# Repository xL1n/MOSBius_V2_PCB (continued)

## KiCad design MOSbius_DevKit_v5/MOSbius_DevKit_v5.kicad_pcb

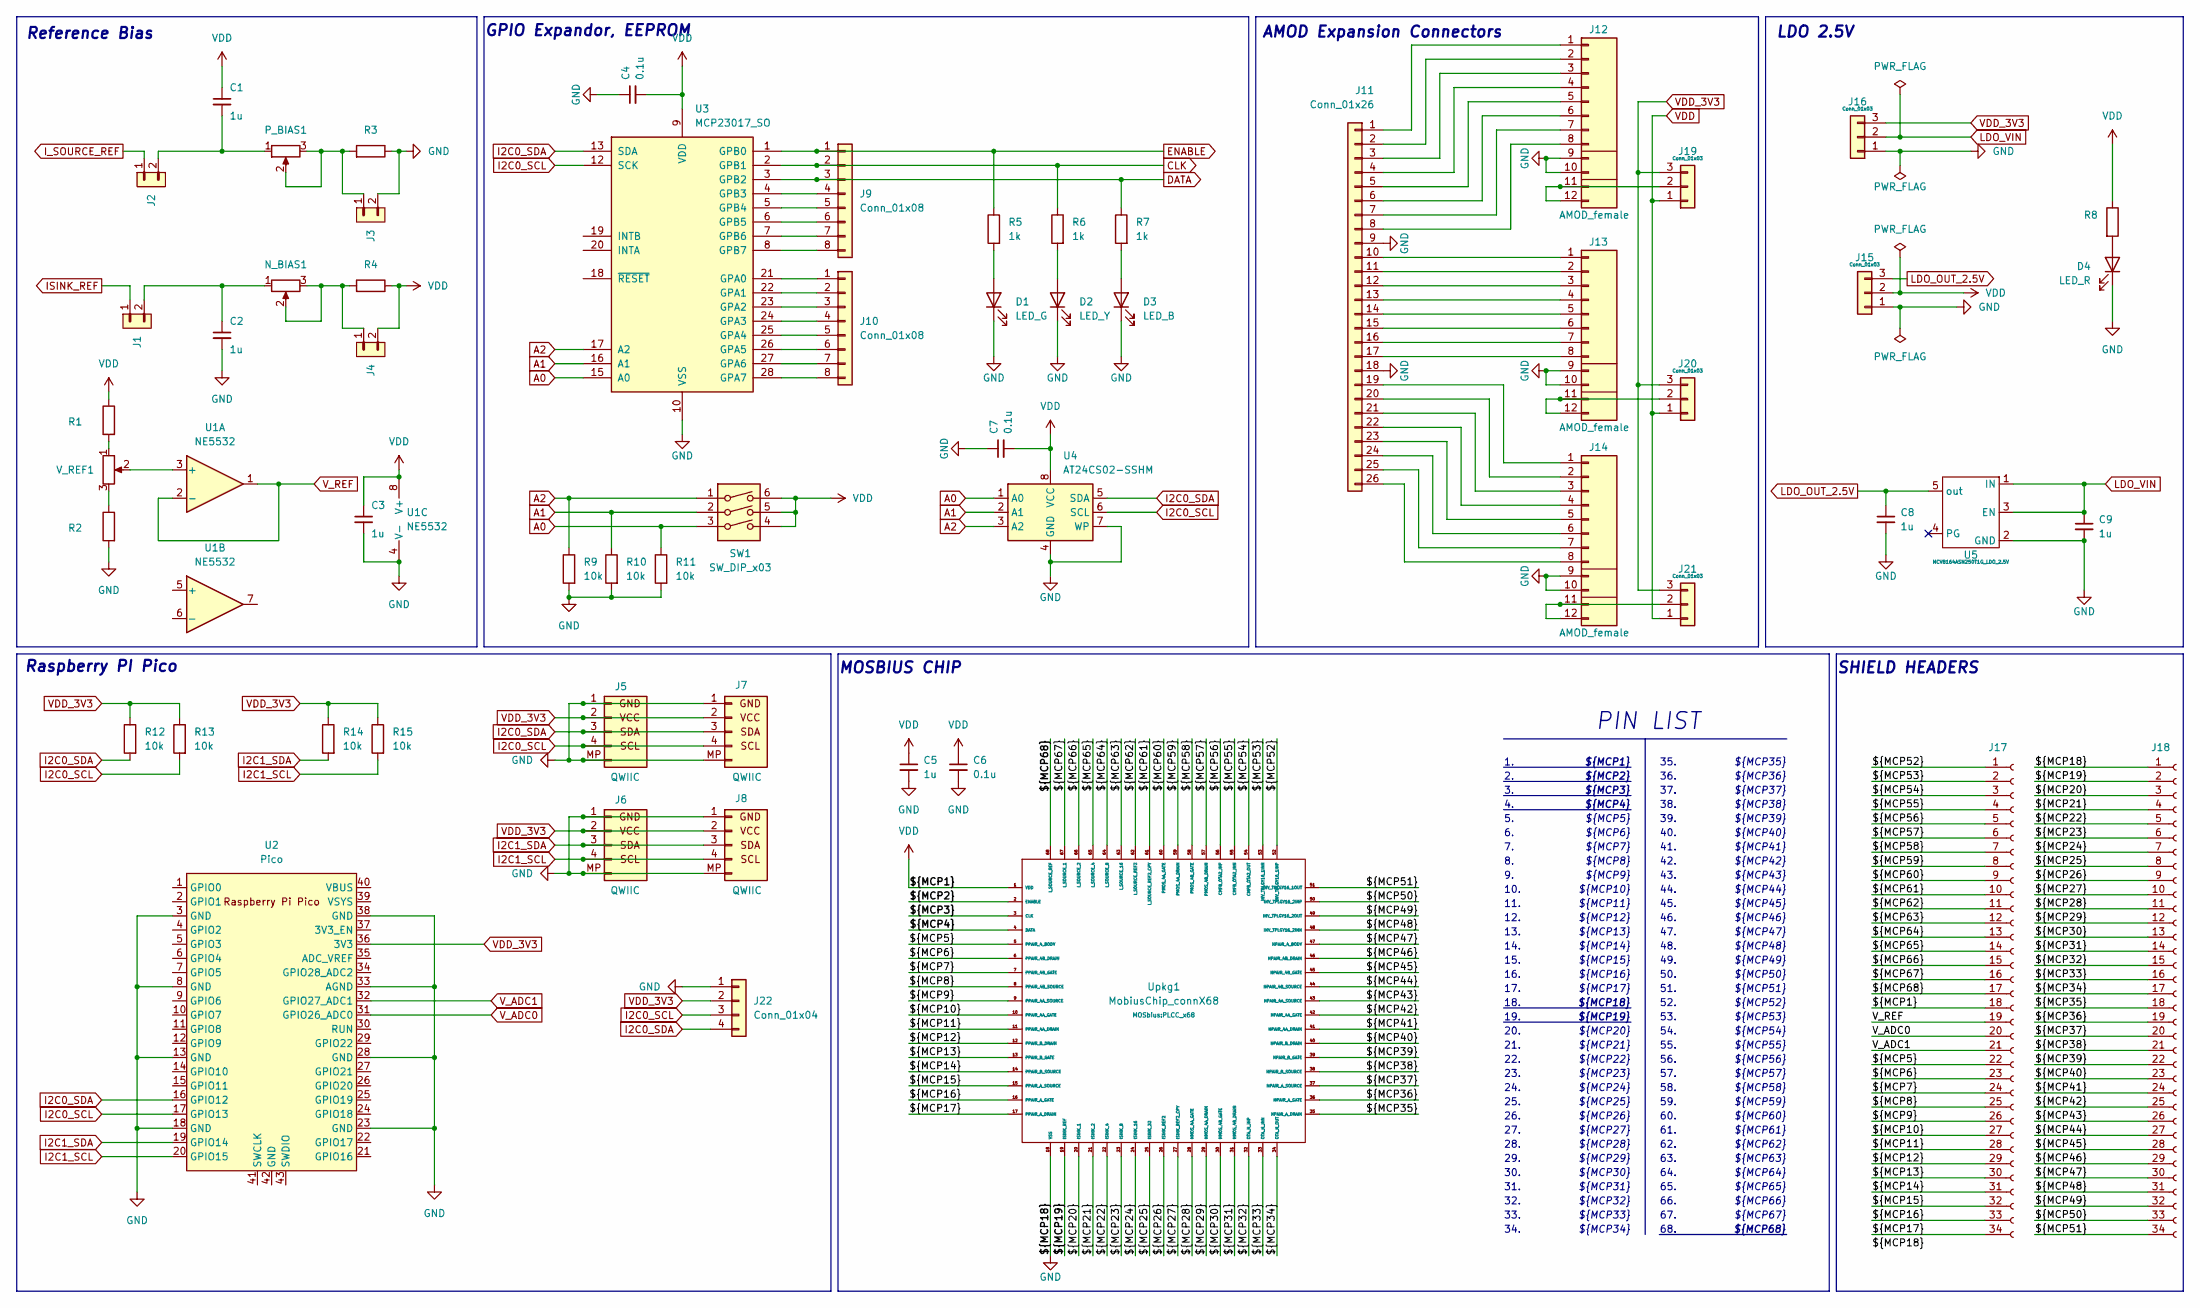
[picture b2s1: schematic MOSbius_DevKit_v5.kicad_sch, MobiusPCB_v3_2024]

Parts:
C1, C2, C3, C5, C8, C9: 1u; C_0603_1608Metric
C4, C6, C7: 0.1u; C_0603_1608Metric
D1: LED_G; LED_0805_2012Metric
D2: LED_Y; LED_0805_2012Metric
D3: LED_B; LED_0805_2012Metric
D4: LED_R; LED_0805_2012Metric
J1, J2, J3, J4: PINHD_1x2_Male; PinHeader_1x02_P2.54mm_Vertical
J5, J6, J7, J8: QWIIC; JST_SH_SM04B-SRSS-TB_1x04-1MP_P1.00mm_Horizontal
J9, J10: Conn_01x08; PinHeader_1x08_P2.54mm_Vertical
J11: Conn_01x26; PinHeader_1x26_P2.54mm_Vertical
J12, J13, J14: AMOD_female
J15, J16, J19, J20, J21: Conn_01x03; PinHeader_1x03_P2.54mm_Vertical
J17, J18: Conn_01x34_Socket; PinHeader_1x34_P2.54mm_Vertical
J22: Conn_01x04; PinHeader_1x04_P2.54mm_Vertical
N_BIAS1: R_Potentiometer; Potentiometer_Bourns_3296W_Vertical
P_BIAS1: R_Potentiometer; Potentiometer_Bourns_3296W_Vertical
R1, R2, R3, R4: 1.3K; R_0603_1608Metric
R5, R6, R7, R8: 1k; R_0603_1608Metric
R9, R10, R11, R12, R13, R14, R15: 10k; R_0603_1608Metric
SW1: SW_DIP_x03; SW_DIP_SPSTx03_Slide_Omron_A6S-310x_W8.9mm_P2.54mm
U1: NE5532
U2: Pico; RPi_Pico_SMD_TH
U3: MCP23017_SO; SOIC-28W_7.5x17.9mm_P1.27mm
U4: AT24CS02-SSHM; SOIC-8_3.9x4.9mm_P1.27mm
U5: NCV8164ASN250T1G_LDO_2.5V; SOT-23-5
Upkg1: MobiusChip_connX68; PLCC_x68
V_REF1: R_Potentiometer; Potentiometer_Bourns_3296W_Vertical

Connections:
/CMFB_OTA2_INN: J17.4, Upkg1.55 (CMFB_OTA2_INN)
/CMFB_OTA2_INP: J17.5, Upkg1.56 (CMFB_OTA2_INP)
/CMFB_OTA2_OUT: J17.3, Upkg1.54 (CMFB_OTA2_OUT)
/INV_TPLGY16_1INN: J17.2, Upkg1.53 (INV_TPLGY16_1INN)
/INV_TPLGY16_1INP: J17.1, Upkg1.52 (INV_TPLGY16_1INP)
/INV_TPLGY16_1OUT: J18.34, Upkg1.51 (INV_TPLGY16_1OUT)
/INV_TPLGY16_2INN: J18.31, Upkg1.48 (INV_TPLGY16_2INN)
/INV_TPLGY16_2INP: J18.33, Upkg1.50 (INV_TPLGY16_2INP)
/INV_TPLGY16_2OUT: J18.32, Upkg1.49 (INV_TPLGY16_2OUT)
/ISINK_1: J18.3, Upkg1.20 (ISINK_1)
/ISINK_2: J18.4, Upkg1.21 (ISINK_2)
/ISINK_4: J18.5, Upkg1.22 (ISINK_4)
/ISINK_8: J18.6, Upkg1.23 (ISINK_8)
/ISINK_16: J18.7, Upkg1.24 (ISINK_16)
/ISINK_32: J18.8, Upkg1.25 (ISINK_32)
/ISINK_REF2: J18.9, Upkg1.26 (ISINK_REF2)
/ISINK_REF2_CPY: J18.10, Upkg1.27 (ISINK_REF2_CPY)
/I_SOURCE_1: J17.16, Upkg1.67 (I_SOURCE_1)
/I_SOURCE_2: J17.15, Upkg1.66 (I_SOURCE_2)
/I_SOURCE_4: J17.14, Upkg1.65 (I_SOURCE_4)
/I_SOURCE_8: J17.13, Upkg1.64 (I_SOURCE_8)
/I_SOURCE_16: J17.12, Upkg1.63 (I_SOURCE_16)
/I_SOURCE_REF2: J17.11, Upkg1.62 (I_SOURCE_REF2)
/I_SOURCE_REF2_CPY: J17.10, Upkg1.61 (I_SOURCE_REF2_CPY)
/NMOS_4A_DRAIN: J18.12, Upkg1.29 (NMOS_4A_DRAIN)
/NMOS_4A_GATE: J18.11, Upkg1.28 (NMOS_4A_GATE)
/NMOS_4B_DRAIN: J18.14, Upkg1.31 (NMOS_4B_DRAIN)
/NMOS_4B_GATE: J18.13, Upkg1.30 (NMOS_4B_GATE)
/NPAIR_4A_DRAIN: J18.24, Upkg1.41 (NPAIR_4A_DRAIN)
/NPAIR_4A_GATE: J18.25, Upkg1.42 (NPAIR_4A_GATE)
/NPAIR_4A_SOURCE: J18.26, Upkg1.43 (NPAIR_4A_SOURCE)
/NPAIR_4B_DRAIN: J18.29, Upkg1.46 (NPAIR_4B_DRAIN)
/NPAIR_4B_GATE: J18.28, Upkg1.45 (NPAIR_4B_GATE)
/NPAIR_4B_SOURCE: J18.27, Upkg1.44 (NPAIR_4B_SOURCE)
/NPAIR_4_BODY: J18.30, Upkg1.47 (NPAIR_4_BODY)
/NPAIR_A_DRAIN: J18.18, Upkg1.35 (NPAIR_A_DRAIN)
/NPAIR_A_GATE: J18.19, Upkg1.36 (NPAIR_A_GATE)
/NPAIR_A_SOURCE: J18.20, Upkg1.37 (NPAIR_A_SOURCE)
/NPAIR_B_DRAIN: J18.23, Upkg1.40 (NPAIR_B_DRAIN)
/NPAIR_B_GATE: J18.22, Upkg1.39 (NPAIR_B_GATE)
/NPAIR_B_SOURCE: J18.21, Upkg1.38 (NPAIR_B_SOURCE)
/OTA_N_INN: J18.16, Upkg1.33 (OTA_N_INN)
/OTA_N_INP: J18.15, Upkg1.32 (OTA_N_INP)
/OTA_N_OUT: J18.17, Upkg1.34 (OTA_N_OUT)
/PMOS_4A_DRAIN: J17.8, Upkg1.59 (PMOS_4A_DRAIN)
/PMOS_4A_GATE: J17.9, Upkg1.60 (PMOS_4A_GATE)
/PMOS_4B_DRAIN: J17.6, Upkg1.57 (PMOS_4B_DRAIN)
/PMOS_4B_GATE: J17.7, Upkg1.58 (PMOS_4B_GATE)
/PPAIR_4A_DRAIN: J17.28, Upkg1.11 (PPAIR_4A_DRAIN)
/PPAIR_4A_GATE: J17.27, Upkg1.10 (PPAIR_4A_GATE)
/PPAIR_4A_SOURCE: J17.26, Upkg1.9 (PPAIR_4A_SOURCE)
/PPAIR_4B_DRAIN: J17.23, Upkg1.6 (PPAIR_4B_DRAIN)
/PPAIR_4B_GATE: J17.24, Upkg1.7 (PPAIR_4B_GATE)
/PPAIR_4B_SOURCE: J17.25, Upkg1.8 (PPAIR_4B_SOURCE)
/PPAIR_4_BODY: J17.22, Upkg1.5 (PPAIR_4_BODY)
/PPAIR_A_DRAIN: J17.34, Upkg1.17 (PPAIR_A_DRAIN)
/PPAIR_A_GATE: J17.33, Upkg1.16 (PPAIR_A_GATE)
/PPAIR_A_SOURCE: J17.32, Upkg1.15 (PPAIR_A_SOURCE)
/PPAIR_B_DRAIN: J17.29, Upkg1.12 (PPAIR_B_DRAIN)
/PPAIR_B_GATE: J17.30, Upkg1.13 (PPAIR_B_GATE)
/PPAIR_B_SOURCE: J17.31, Upkg1.14 (PPAIR_B_SOURCE)
A0: R11.1, SW1.3, U3.15 (A0), U4.1 (A0)
A1: R10.1, SW1.2, U3.16 (A1), U4.2 (A1)
A2: R9.1, SW1.1, U3.17 (A2), U4.3 (A2)
GND: C2.2, C3.2, C4.1, C5.2, C6.2, C7.1, C8.2, C9.2, D1.1 (K), D2.1 (K), D3.1 (K), D4.1 (K), J3.2, J5.1, J5.MP, J6.1, J6.MP, J7.1, J7.MP, J8.1, J8.MP, J11.9, J11.18, J12.9, J12.10, J13.9, J13.10, J14.9, J14.10, J15.1, J16.1, J18.1, J22.1, R2.2, R3.1, R9.2, R10.2, R11.2, U1.4 (V-), U2.3 (GND), U2.8 (GND), U2.13 (GND), U2.18 (GND), U2.23 (GND), U2.28 (GND), U2.33 (AGND), U2.38 (GND), U3.10 (VSS), U4.4 (GND), U4.7 (WP), U5.2 (GND), Upkg1.18 (VSS)
I2C0_SCL: J5.4, J7.4, J22.3, R13.2, U2.17 (GPIO13), U3.12 (SCK), U4.6 (SCL)
I2C0_SDA: J5.3, J7.3, J22.4, R12.2, U2.16 (GPIO12), U3.13 (SDA), U4.5 (SDA)
I2C1_SCL: J6.4, J8.4, R15.2, U2.20 (GPIO15)
I2C1_SDA: J6.3, J8.3, R14.2, U2.19 (GPIO14)
LDO_OUT_2.5V: C8.1, J15.3, U5.5 (out)
LDO_VIN: C9.1, J16.2, U5.1 (IN), U5.3 (EN)
unnamed: C1.2, J2.2, P_BIAS1.1
unnamed: C2.1, J1.2, N_BIAS1.1
unnamed: D1.2 (A), R5.2
unnamed: D2.2 (A), R6.2
unnamed: D3.2 (A), R7.2
unnamed: D4.2 (A), R8.2
unnamed: J3.1, P_BIAS1.2, P_BIAS1.3, R3.2
unnamed: J4.1, N_BIAS1.2, N_BIAS1.3, R4.2
unnamed: J9.4, U3.4 (GPB3)
unnamed: J9.5, U3.5 (GPB4)
unnamed: J9.6, U3.6 (GPB5)
unnamed: J9.7, U3.7 (GPB6)
unnamed: J9.8, U3.8 (GPB7)
unnamed: J10.1, U3.21 (GPA0)
unnamed: J10.2, U3.22 (GPA1)
unnamed: J10.3, U3.23 (GPA2)
unnamed: J10.4, U3.24 (GPA3)
unnamed: J10.5, U3.25 (GPA4)
unnamed: J10.6, U3.26 (GPA5)
unnamed: J10.7, U3.27 (GPA6)
unnamed: J10.8, U3.28 (GPA7)
unnamed: J11.1, J12.1
unnamed: J11.2, J12.2
unnamed: J11.3, J12.3
unnamed: J11.4, J12.4
unnamed: J11.5, J12.5
unnamed: J11.6, J12.6
unnamed: J11.7, J12.7
unnamed: J11.8, J12.8
unnamed: J11.10, J13.1
unnamed: J11.11, J13.2
unnamed: J11.12, J13.3
unnamed: J11.13, J13.4
unnamed: J11.14, J13.5
unnamed: J11.15, J13.6
unnamed: J11.16, J13.7
unnamed: J11.17, J13.8
unnamed: J11.19, J14.1
unnamed: J11.20, J14.2
unnamed: J11.21, J14.3
unnamed: J11.22, J14.4
unnamed: J11.23, J14.5
unnamed: J11.24, J14.6
unnamed: J11.25, J14.7
unnamed: J11.26, J14.8
unnamed: J12.11, J12.12, J19.2
unnamed: J13.11, J13.12, J20.2
unnamed: J14.11, J14.12, J21.2
unnamed: R1.2, V_REF1.1
unnamed: R2.1, V_REF1.3
unnamed: U1.3 (+), V_REF1.2
VDD: C1.1, C3.1, C4.2, C5.1, C6.1, C7.2, J4.2, J15.2, J17.18, J19.1, J20.1, J21.1, R1.1, R4.1, R8.1, SW1.4, SW1.5, SW1.6, U1.8 (V+), U3.9 (VDD), U4.8 (VCC), Upkg1.1 (VDD)
VDD_3V3: J5.2, J6.2, J7.2, J8.2, J16.3, J19.3, J20.3, J21.3, J22.2, R12.1, R13.1, R14.1, R15.1, U2.36 (3V3)
V_ADC0: J17.20, U2.31 (GPIO26_ADC0)
V_ADC1: J17.21, U2.32 (GPIO27_ADC1)
V_REF: J17.19, U1.1, U1.2 (-)

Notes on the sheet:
${MCP9}
18.
${MCP61}
${MCP12}
65.
SHIELD HEADERS
58.
39.
12.
55.
${MCP66}
${MCP39}
${MCP55}
${MCP35}
59.
${MCP57}
${MCP43}
44.
${MCP27}
14.
${MCP46}
19.
60.
${MCP44}
${MCP37}
66.
41.
42.
31.
${MCP4}
22.
Raspberry PI Pico
${MCP18}
Reference Bias
40.
${MCP7}
${MCP34}
${MCP51}
16.
PIN LIST

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
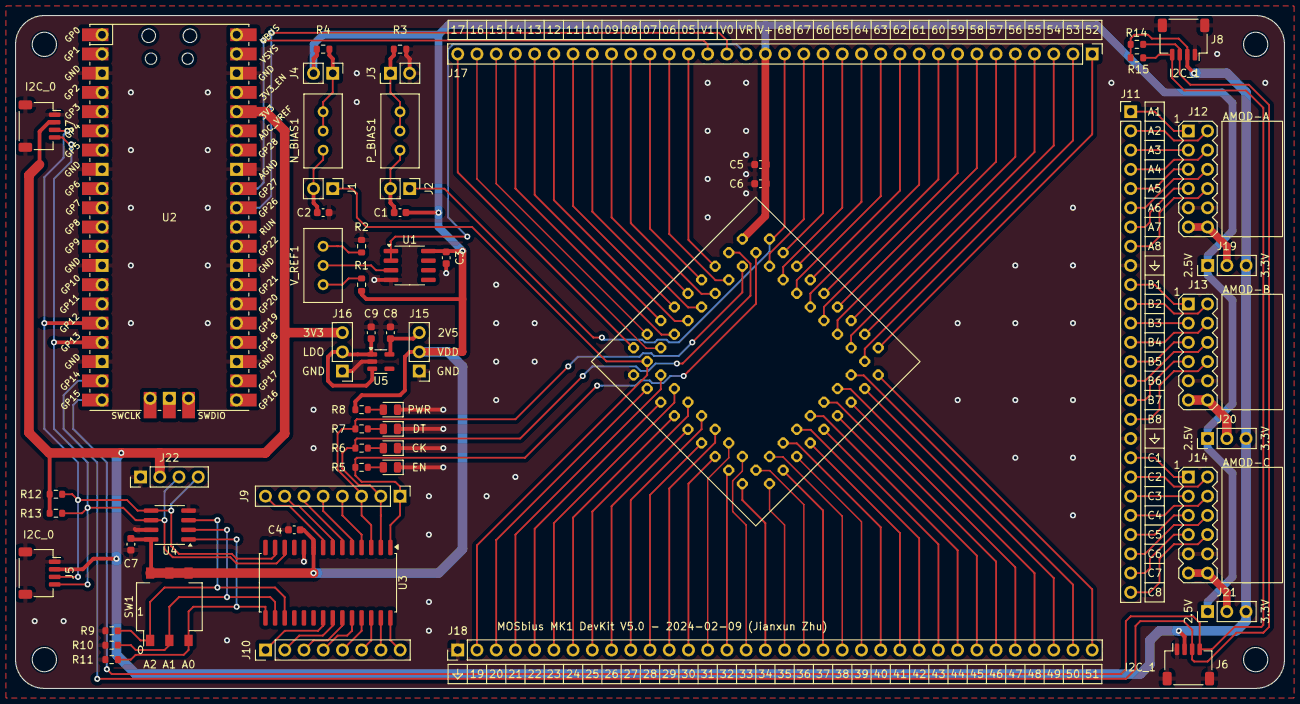
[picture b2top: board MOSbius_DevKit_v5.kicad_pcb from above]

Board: 2 copper layers, 167.6 x 88.9 mm, 64 parts (0 on the bottom side), 132 nets.

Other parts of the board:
H1, H2, H3, H4: MountingHole; MountingHole_3.2mm_M3_ISO7380

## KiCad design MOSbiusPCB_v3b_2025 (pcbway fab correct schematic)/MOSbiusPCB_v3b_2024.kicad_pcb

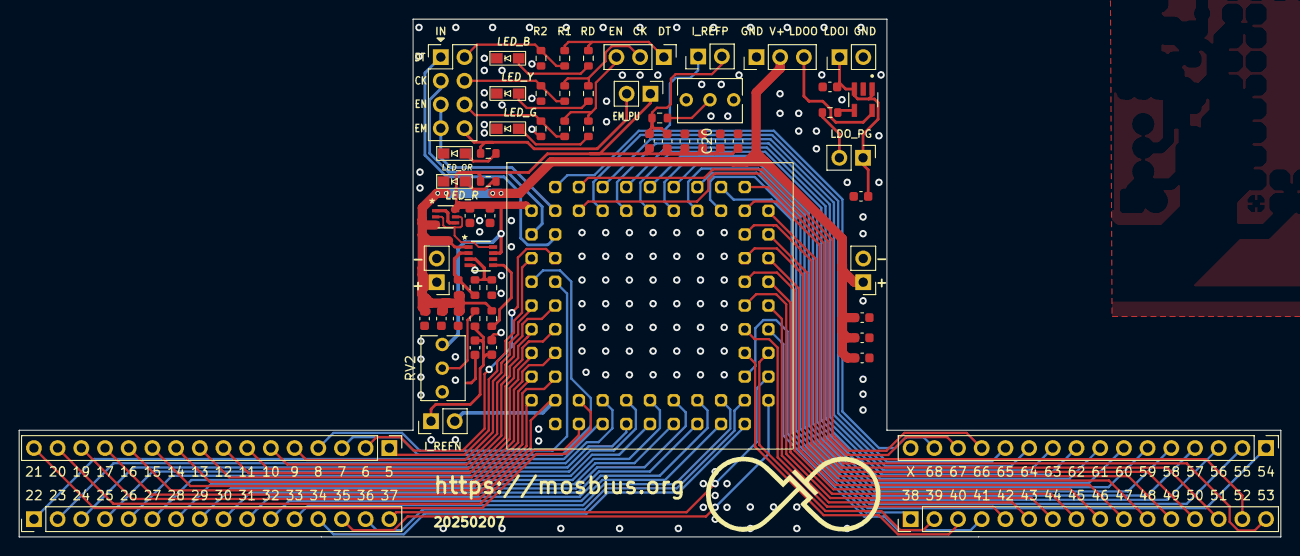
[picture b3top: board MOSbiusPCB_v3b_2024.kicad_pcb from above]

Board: 2 copper layers, 135.3 x 55.5 mm, 61 parts (0 on the bottom side), 94 nets.

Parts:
C1, C4, C6, C8, C9, C15, C18: 1u; C_0603_1608Metric
C2, C3, C7, C10, C16, C17: 0.1u; C_0603_1608Metric
C5, C12, C14, C19: 10u; C_0603_1608Metric
C20: 47u; C_0603_1608Metric
D1: LED_OR; SunLED_LED_XZC_0805
D2: LED_G; SunLED_LED_XZC_0805
D3: LED_Y; SunLED_LED_XZC_0805
D4: LED_B; SunLED_LED_XZC_0805
D5: LED_R; SunLED_LED_XZC_0805
J1, J2, J3, J4: Conn_01x16_Pin; PinHeader_1x16_P2.54mm_Vertical
J5, J7, J8: PINHD_1x2_Male; PinHeader_1x02_P2.54mm_Vertical
J6: Conn_01x02_Pin; PinHeader_1x02_P2.54mm_Vertical
J10: Conn_02x04_Row_Letter_First; PinHeader_2x04_P2.54mm_Vertical
J14_GND2, J14_GND3: Conn_01x03; PinHeader_1x03_P2.54mm_Vertical
J18_VDC1: Conn_01x02; PinHeader_1x02_P2.54mm_Vertical
JP1_LDOPG1, JP2_EN1: Jumper_2_Open; PinHeader_1x02_P2.54mm_Vertical
R1, R3, R5, R11, R18: 1.1k; R_0603_1608Metric
R2, R4, R6: 3.3k; R_0603_1608Metric
R7, R9, R17, R19: 330; R_0603_1608Metric
R8: 750; R_0603_1608Metric
R10: 10K; R_0603_1608Metric
R13, R16: 0; R_0603_1608Metric
R14: 510K; R_0603_1608Metric
R15: 120K; R_0603_1608Metric
RV1, RV2: 25k_POT; Potentiometer_Bourns_3266Y_Vertical
U1: NCV8164ASN250T1G_LDO_2.5V; NCV8164ASN250T1G
U2: LTC4365TS8; TSOT-23_TS8_LIT
U3: UM6K34NTCN; TRANS_UM6J1_ROM
Upkg1: MobiusChip_connX68; PLCC_x68

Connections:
/CMFB_OTA2_INN: J4.2, Upkg1.55 (CMFB_OTA2_INN)
/CMFB_OTA2_INP: J4.3, Upkg1.56 (CMFB_OTA2_INP)
/CMFB_OTA2_OUT: J4.1, Upkg1.54 (CMFB_OTA2_OUT)
/INV_TPLGY16_1INN: J3.16, Upkg1.53 (INV_TPLGY16_1INN)
/INV_TPLGY16_1INP: J3.15, Upkg1.52 (INV_TPLGY16_1INP)
/INV_TPLGY16_1OUT: J3.14, Upkg1.51 (INV_TPLGY16_1OUT)
/INV_TPLGY16_2INN: J3.11, Upkg1.48 (INV_TPLGY16_2INN)
/INV_TPLGY16_2INP: J3.13, Upkg1.50 (INV_TPLGY16_2INP)
/INV_TPLGY16_2OUT: J3.12, Upkg1.49 (INV_TPLGY16_2OUT)
/ISINK_1: J1.15, Upkg1.20 (ISINK_1)
/ISINK_2: J1.16, Upkg1.21 (ISINK_2)
/ISINK_4: J2.1, Upkg1.22 (ISINK_4)
/ISINK_8: J2.2, Upkg1.23 (ISINK_8)
/ISINK_16: J2.3, Upkg1.24 (ISINK_16)
/ISINK_32: J2.4, Upkg1.25 (ISINK_32)
/ISINK_REF2: J2.5, Upkg1.26 (ISINK_REF2)
/ISINK_REF2_CPY: J2.6, Upkg1.27 (ISINK_REF2_CPY)
/I_SOURCE_1: J4.14, Upkg1.67 (I_SOURCE_1)
/I_SOURCE_2: J4.13, Upkg1.66 (I_SOURCE_2)
/I_SOURCE_4: J4.12, Upkg1.65 (I_SOURCE_4)
/I_SOURCE_8: J4.11, Upkg1.64 (I_SOURCE_8)
/I_SOURCE_16: J4.10, Upkg1.63 (I_SOURCE_16)
/I_SOURCE_REF2: J4.9, Upkg1.62 (I_SOURCE_REF2)
/I_SOURCE_REF2_CPY: J4.8, Upkg1.61 (I_SOURCE_REF2_CPY)
/NMOS_4A_DRAIN: J2.8, Upkg1.29 (NMOS_4A_DRAIN)
/NMOS_4A_GATE: J2.7, Upkg1.28 (NMOS_4A_GATE)
/NMOS_4B_DRAIN: J2.10, Upkg1.31 (NMOS_4B_DRAIN)
/NMOS_4B_GATE: J2.9, Upkg1.30 (NMOS_4B_GATE)
/NPAIR_4A_DRAIN: J3.4, Upkg1.41 (NPAIR_4A_DRAIN)
/NPAIR_4A_GATE: J3.5, Upkg1.42 (NPAIR_4A_GATE)
/NPAIR_4A_SOURCE: J3.6, Upkg1.43 (NPAIR_4A_SOURCE)
/NPAIR_4B_DRAIN: J3.9, Upkg1.46 (NPAIR_4B_DRAIN)
/NPAIR_4B_GATE: J3.8, Upkg1.45 (NPAIR_4B_GATE)
/NPAIR_4B_SOURCE: J3.7, Upkg1.44 (NPAIR_4B_SOURCE)
/NPAIR_4_BODY: J3.10, Upkg1.47 (NPAIR_4_BODY)
/NPAIR_A_DRAIN: J2.14, Upkg1.35 (NPAIR_A_DRAIN)
/NPAIR_A_GATE: J2.15, Upkg1.36 (NPAIR_A_GATE)
/NPAIR_A_SOURCE: J2.16, Upkg1.37 (NPAIR_A_SOURCE)
/NPAIR_B_DRAIN: J3.3, Upkg1.40 (NPAIR_B_DRAIN)
/NPAIR_B_GATE: J3.2, Upkg1.39 (NPAIR_B_GATE)
/NPAIR_B_SOURCE: J3.1, Upkg1.38 (NPAIR_B_SOURCE)
/OTA_N_INN: J2.12, Upkg1.33 (OTA_N_INN)
/OTA_N_INP: J2.11, Upkg1.32 (OTA_N_INP)
/OTA_N_OUT: J2.13, Upkg1.34 (OTA_N_OUT)
/PMOS_4A_DRAIN: J4.6, Upkg1.59 (PMOS_4A_DRAIN)
/PMOS_4A_GATE: J4.7, Upkg1.60 (PMOS_4A_GATE)
/PMOS_4B_DRAIN: J4.4, Upkg1.57 (PMOS_4B_DRAIN)
/PMOS_4B_GATE: J4.5, Upkg1.58 (PMOS_4B_GATE)
/PPAIR_4A_DRAIN: J1.7, Upkg1.11 (PPAIR_4A_DRAIN)
/PPAIR_4A_GATE: J1.6, Upkg1.10 (PPAIR_4A_GATE)
/PPAIR_4A_SOURCE: J1.5, Upkg1.9 (PPAIR_4A_SOURCE)
/PPAIR_4B_DRAIN: J1.2, Upkg1.6 (PPAIR_4B_DRAIN)
/PPAIR_4B_GATE: J1.3, Upkg1.7 (PPAIR_4B_GATE)
/PPAIR_4B_SOURCE: J1.4, Upkg1.8 (PPAIR_4B_SOURCE)
/PPAIR_4_BODY: J1.1, Upkg1.5 (PPAIR_4_BODY)
/PPAIR_A_DRAIN: J1.13, Upkg1.17 (PPAIR_A_DRAIN)
/PPAIR_A_GATE: J1.12, Upkg1.16 (PPAIR_A_GATE)
/PPAIR_A_SOURCE: J1.11, Upkg1.15 (PPAIR_A_SOURCE)
/PPAIR_B_DRAIN: J1.8, Upkg1.12 (PPAIR_B_DRAIN)
/PPAIR_B_GATE: J1.9, Upkg1.13 (PPAIR_B_GATE)
/PPAIR_B_SOURCE: J1.10, Upkg1.14 (PPAIR_B_SOURCE)
CLK: J10.3, Upkg1.3 (CLK)
CLK_CVRT_2.5V: J10.4, R3.2, R4.1
CLK_CVRT_3.3V: J14_GND2.2, R3.1, R8.1
DATA: J10.1, Upkg1.4 (DATA)
DATA_CVRT_2.5V: J10.2, R5.2, R6.1
DATA_CVRT_3.3V: J14_GND2.1, R5.1, R9.1
ENABLE: J10.5, J10.7, Upkg1.2 (ENABLE)
EN_CVRT_2.5V: J10.6, R1.2, R2.1
EN_CVRT_3.3V: J14_GND2.3, R1.1, R7.1
EN_MAN_2.5V: J10.8, JP2_EN1.2 (B), R19.1
GND: C1.2, C2.2, C4.2, C5.2, C6.2, C7.2, C9.2, C10.2, C12.2, C14.2, C15.2, C16.2, C17.2, C18.2, C19.2, C20.2, D1.1 (K), D2.1 (K), D3.1 (K), D4.1 (K), D5.1 (K), J5.2, J6.2, J14_GND3.1, J18_VDC1.2, R2.2, R4.2, R6.2, R15.2, RV1.3, U1.2 (GND), U2.4 (GND), Upkg1.18 (VSS)
ISINK_REF: J1.14, J7.2, Upkg1.19 (ISINK_REF)
I_SOURCE_REF: J4.15, J8.1, Upkg1.68 (I_SOURCE_REF)
LDO_OUT_2.5V: J14_GND3.3, U1.5 (out)
LDO_PG_2.5V: R10.1, U1.4 (PG)
LDO_VIN: C4.1, C5.1, J18_VDC1.1, JP1_LDOPG1.1 (A), U1.1 (IN), U1.3 (EN)
unnamed: C1.1, C2.1, J7.1, R18.2
unnamed: C3.2, C8.2, J8.2, R11.2
unnamed: D1.2 (A), R19.2
unnamed: D2.2 (A), R7.2
unnamed: D3.2 (A), R8.2
unnamed: D4.2 (A), R9.2
unnamed: D5.2 (A), R17.2
unnamed: JP1_LDOPG1.2 (B), R10.2
unnamed: R11.1, RV1.2
unnamed: R18.1, RV2.2
unnamed: U2.8 (GATE), U3.2, U3.5
unnamed: R14.2, R15.1, U2.3 (OV)
unnamed: R13.2, R14.1, U2.2 (UV)
unnamed: R16.2, U2.5 (~SHDN)
unnamed: U3.1, U3.4
VD: C9.1, C10.1, C12.1, C14.1, C15.1, C16.1, J5.1, J6.1, J14_GND3.2, R13.1, R16.1, U2.1 (Vin), U3.3
VDD: C3.1, C6.1, C7.1, C8.1, C17.1, C18.1, C19.1, C20.1, JP2_EN1.1 (A), R17.1, RV2.1, U2.7 (Vout), U3.6, Upkg1.1 (VDD)
